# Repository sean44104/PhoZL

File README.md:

# PhobGCCv2-HW
Seperate repository for the hardware used in the PhobGCC v2.0

The PhobGCC v2.0 board is licensed under CERN Open Hardware Licence Version 2 - Strongly Reciprocal.
This means that any changes made to the board should be made public and CHANGES.txt be updated to reflect said changes.

# CHANGES.txt
PhoZL is a version of the PhobGCCv2 PCB that adds a footprint for a left z button to the board, connecting to GND and GPIO12

In order to make these changes possible, the edge cuts and the tracks inside of the PCB have been modified; these changes are self evident.

PCB Ordering Guide: https://github.com/PhobGCC/PhobGCC-doc/blob/main/For_Makers/Phob2_JLCPCB_Ordering_Guide.md

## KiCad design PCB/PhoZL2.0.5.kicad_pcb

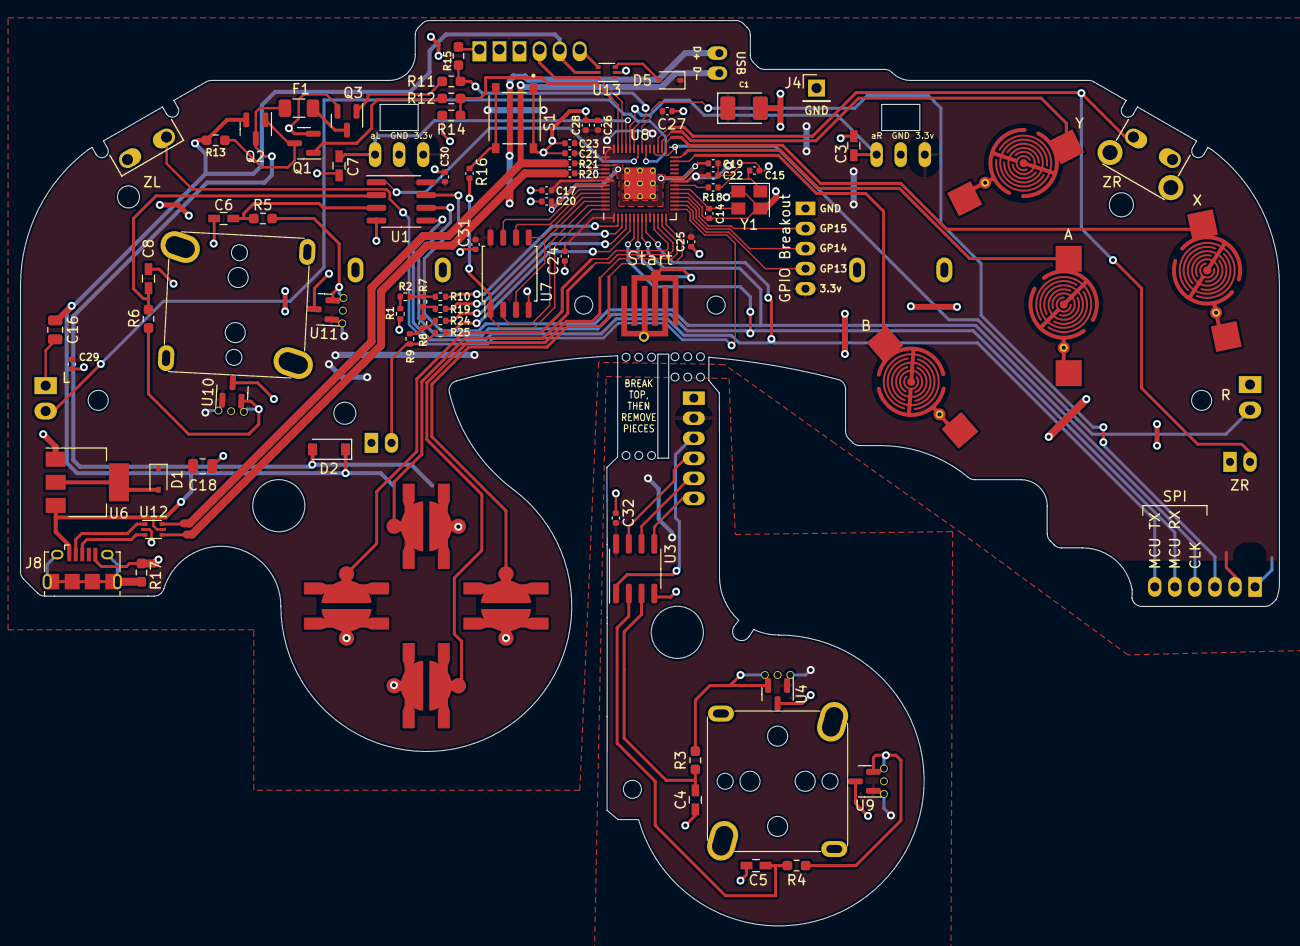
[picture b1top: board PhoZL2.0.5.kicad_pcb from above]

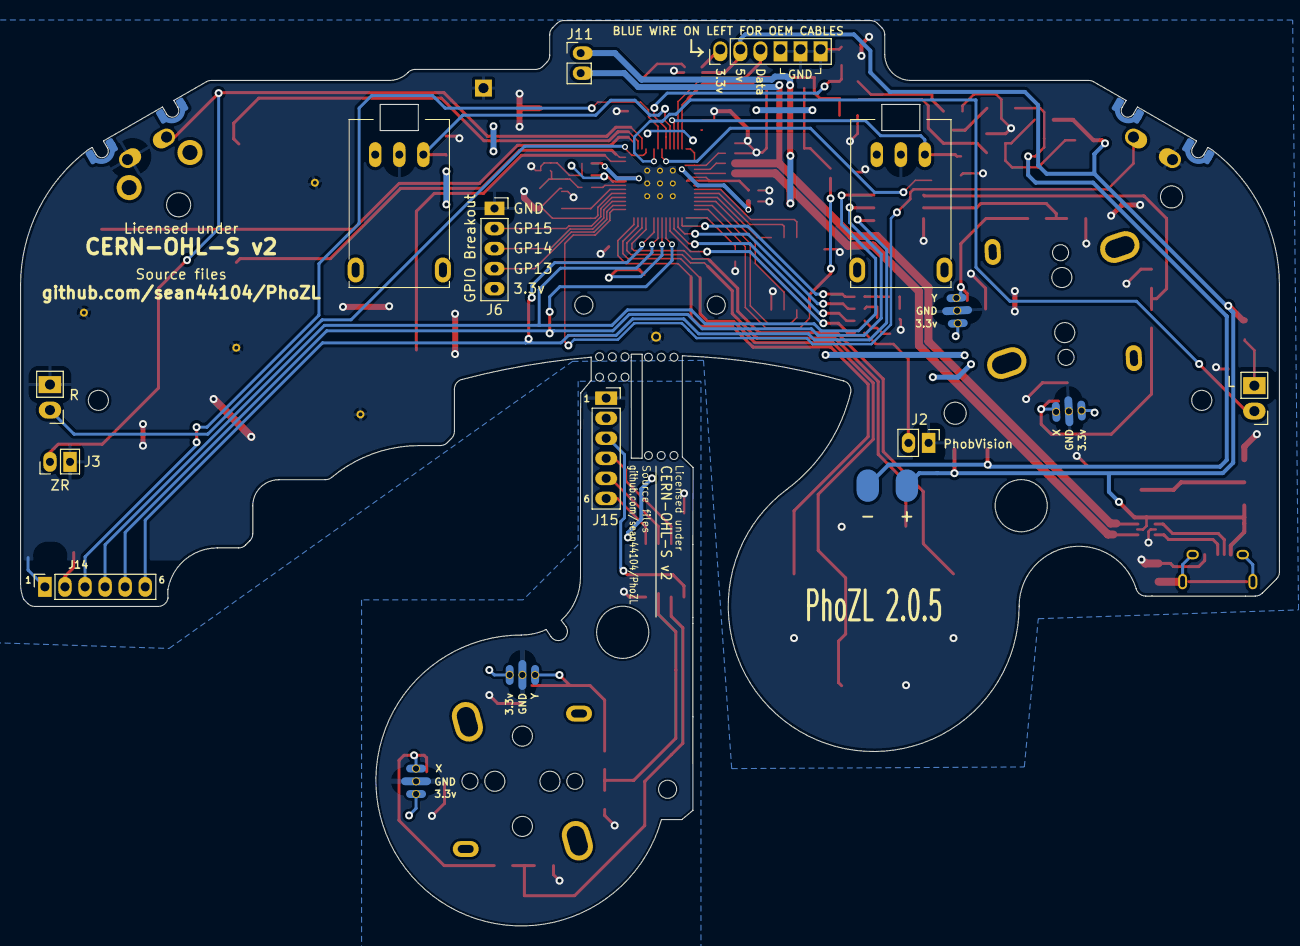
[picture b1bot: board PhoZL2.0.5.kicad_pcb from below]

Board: 2 copper layers, 125.5 x 90.3 mm, 111 parts (12 on the bottom side), 78 nets.

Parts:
C1: 47u; CP_EIA-3528-12_Kemet-T_Pad1.50x2.35mm_HandSolder
C3, C4, C5, C6, C7, C8: 0.047u; C_0603_HandSoldering
C14, C15: 27p; C_0402_1005Metric
C16, C18: 10u; C_0805_2012Metric
C17, C19, C20, C22, C24, C25, C26, C27, C28, C29, C30, C31, C32: 100n; C_0402_1005Metric
C21, C23: 1u; C_0402_1005Metric
D1, D5: CUS10S30,H3F; D_SOD-323
D2: M7C; D_SOD-123
F1: Fuse; Fuse_1206_3216Metric
H1: 5.2mm; MountingHole_5.2mm
H2: Slot
H3, H4: 2mm; MountingHole_2.0mm
H5, H6: 1.8mm; MountingHole_1.8mm
H7: 2.4mm; MountingHole_2.4mm
H8, H9: 2.2mm; MountingHole_2.2mm
H10: MountingHole; MountingHole_1.8mm
H11: MountingHole; MountingHole_5.2mm
H12, H13: MountingHole; MountingHole_2.0mm
H14: MouseBite; breakaway-mousebites-double-v2-small
H15: MouseBite; breakaway-mousebites-double-v2-large
J1: Conn_01x06_Female; GCC_Header_Straight_1x06_Pitch2.00mm
J2, J11: Conn_01x02; PinHeader_1x02_P2.00mm_Vertical
J3: Conn_01x02; PinHeader_1x02_P2.00mm_Horizontal
J4: Conn_01x01; PinHeader_1x01_P2.54mm_Vertical
J5: Rumble; rumble_pins
J6, J14, J15: Conn_01x06; PinSocket_1x06_P2.00mm_Vertical
J8: USB_B_Micro; USB_Micro-B_Amphenol_10118194_Horizontal
Q1, Q3: Q_NMOS_GSD; SOT-23
Q2: Q_PMOS_GDS; SOT-23
R1, R2, R7, R8, R9: 180; R_0402_1005Metric
R3, R4, R5, R6: 2k; R_0603_1608Metric_Pad0.98x0.95mm_HandSolder
R10, R19, R24, R25: 316; R_0402_1005Metric
R11, R12: 100R; R_0603_1608Metric_Pad0.98x0.95mm_HandSolder
R13, R14, R15: 10k; R_0603_1608Metric_Pad0.98x0.95mm_HandSolder
R16, R18: 1k; C_0402_1005Metric
R17: 100k; R_0603_1608Metric_Pad0.98x0.95mm_HandSolder
R20, R21: 27; C_0402_1005Metric
RV1, RV2: R_POT_MountingPin; GCC_Slider
S1: BOOTSEL; SW_TS-1187A-B-A-B
SW1: A; ABXY_Contact_Omron_Switch_Circley
SW2: B; ABXY_Contact_Omron_Switch_Circley
SW3: X; ABXY_Contact_Omron_Switch_Circley
SW4: Y; ABXY_Contact_Omron_Switch_Circley
SW5: Start; Start_Contact
SW6: L; Pin_Header_Straight_1x02_Pitch2.54mm
SW7: R; Pin_Header_Straight_1x02_Pitch2.54mm
SW8, SW8#2: Z; Z_Switch_Edge_Omron
SW9: Dleft; Dpad_Contact_TL3315NF_2
SW10: Dup; Dpad_Contact_TL3315NF_2
SW11: Dright; Dpad_Contact_TL3315NF_2
SW12: Ddown; Dpad_Contact_TL3315NF_2
U1, U3: MCP3202; SOIC-8_3.9x4.9mm_P1.27mm
U2: Stickbox_Assembly_Main; GCC_Stickbox_Hall_Only
U4, U9, U10, U11: DRV5055A3xDBZxQ1; SOT-23
U5: Stickbox_Assembly_CStick; GCC_Stickbox_Hall_Only
U6: AMS1117-3.3; SOT-223-3_TabPin2
U7: W25Q128JVS; SOIC-8_5.23x5.23mm_P1.27mm
U8: RP2040; RP2040-QFN-56
U12, U13: USBLC6-2P6; SOT-666
Y1: Crystal_GND24; Crystal_SMD_3225-4Pin_3.2x2.5mm

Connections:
+1V1: C19.1, C20.1, C21.1, U8.23 (DVDD), U8.45 (VREG_VOUT), U8.50 (DVDD)
+3V3: C1.1, C17.1, C18.1, C22.1, C23.1, C24.1, C25.1, C26.1, C27.1, C28.1, C29.1, C30.1, C31.1, D1.1 (K), D5.1 (K), J6.2, J14.2, RV1.1 (V+), RV2.1 (V+), U1.8 (VDD/VREF), U2.1 (H1XV), U2.4 (H1YV), U7.8 (VCC), U8.1 (IOVDD), U8.10 (IOVDD), U8.22 (IOVDD), U8.33 (IOVDD), U8.42 (IOVDD), U8.43 (ADC_AVDD), U8.44 (VREG_IN), U8.48 (USB_VDD), U8.49 (IOVDD), U10.1 (VCC), U11.1 (VCC)
+5V: C16.1, D2.1 (K), J1.2, J5.1, J8.1 (VBUS), Q2.2 (S), R13.2, U6.3 (VI), U12.5 (VBUS), U13.5 (VBUS)
/A: SW1.1, U8.28 (GPIO17)
/B: SW2.1, U8.27 (GPIO16)
/Brake: R12.1, R14.2, U8.41 (GPIO29_ADC3)
/CLK: J14.4, U1.7 (CLK), U8.8 (GPIO6)
/CLK2: J15.4, U3.7 (CLK)
/CS1: U1.1 (~CS/SHDN), U8.36 (GPIO24)
/CS2: J14.3, U8.35 (GPIO23)
/CS2_2: J15.3, U3.1 (~CS/SHDN)
/C_x_filt: C5.1, R4.1, U3.2 (CH0)
/C_y_filt: C4.1, R3.1, U3.3 (CH1)
/Ddown: SW12.1, U8.13 (GPIO10)
/Din: J14.6, U1.5 (DIN), U8.9 (GPIO7)
/Din2: J15.6, U3.5 (DIN)
/Dleft: SW9.1, U8.11 (GPIO8)
/Dout: J14.5, U1.6 (DOUT), U8.6 (GPIO4)
/Dout2: J15.5, U3.6 (DOUT)
/Dright: SW11.1, U8.14 (GPIO11)
/Dup: SW10.1, U8.12 (GPIO9)
/GCC_3.3V: J1.1, U13.4 (I/O2)
/GCC_DATA: J1.3, U8.40 (GPIO28_ADC2), U13.6 (I/O1)
/GND_C: C4.2, C5.2, C32.2, J15.1, U3.4 (VSS), U4.3 (GND), U5.2 (H1XG), U5.5 (H1YG), U9.3 (GND)
/GPIO12: SW8#2.2, U8.15 (GPIO12)
/GPIO13: J6.3, U8.16 (GPIO13)
/GPIO14: J6.4, U8.17 (GPIO14)
/GPIO15: J6.5, U8.18 (GPIO15)
/H1XS: R6.2, U2.3 (H1XS), U10.2 (OUT)
/H1YS: R5.2, U2.6 (H1YS), U11.2 (OUT)
/H2XS: R4.2, U5.3 (H1XS), U9.2 (OUT)
/H2YS: R3.2, U4.2 (OUT), U5.6 (H1YS)
/L: SW6.1, U8.34 (GPIO22)
/Ladder1: R10.2, U8.2 (GPIO0)
/Ladder2: R19.2, U8.3 (GPIO1)
/Ladder3: R24.2, U8.4 (GPIO2)
/Ladder4: R25.2, U8.5 (GPIO3)
/Lanalog: C7.1, RV1.3 (Signal), U8.39 (GPIO27_ADC1)
/QSPI_SCLK: U7.6 (CLK), U8.52 (QSPI_SCLK)
/QSPI_SD0: U7.5 (DI(IO0)), U8.53 (QSPI_SD0)
/QSPI_SD1: U7.2 (DO(IO1)), U8.55 (QSPI_SD1)
/QSPI_SD2: U7.3 (IO2), U8.54 (QSPI_SD2)
/QSPI_SD3: U7.7 (IO3), U8.51 (QSPI_SD3)
/QSPI_SS: R16.1, U7.1 (~CS), U8.56 (QSPI_SS)
/R: SW7.1, U8.32 (GPIO21)
/Ranalog: C3.1, RV2.3 (Signal), U8.38 (GPIO26_ADC0)
/Rumble: R11.1, R15.2, U8.37 (GPIO25)
/Start: SW5.1, U8.7 (GPIO5)
/Stick_x_filt: C8.1, R6.1, U1.2 (CH0)
/Stick_y_filt: C6.1, R5.1, U1.3 (CH1)
/USB_D+: J11.1, R20.1, U12.4 (I/O2)
/USB_D+_Raw: J8.3 (D+), U12.3 (I/O2)
/USB_D-: J11.2, R21.1, U12.6 (I/O1)
/USB_D-_Raw: J8.2 (D-), U12.1 (I/O1)
/V: J2.2, R9.1, R25.1
/X: SW3.1, U8.29 (GPIO18)
/XIN: C14.1, U8.20 (XIN), Y1.3
/XOUT: R18.1, U8.21 (XOUT)
/Y: SW4.1, U8.30 (GPIO19)
/Z: J3.2, SW8.1, U8.31 (GPIO20)
/~USB_BOOT: R16.2, S1.C, S1.D
GND: C1.2, C3.2, C6.2, C7.2, C8.2, C14.2, C15.2, C16.2, C17.2, C18.2, C19.2, C20.2, C21.2, C22.2, C23.2, C24.2, C25.2, C26.2, C27.2, C28.2, C29.2, C30.2, C31.2, J1.4, J1.5, J1.6, J2.1, J3.1, J4.1, J6.6, J8.5 (GND), J14.1, Q1.2 (S), Q3.2 (S), R1.2, R14.1, R15.1, R17.2, RV1.2 (GND), RV2.2 (GND), S1.A, S1.B, SW1.2, SW2.2, SW3.2, SW4.2, SW5.2, SW6.2, SW7.2, SW8.2, SW8#2.1, SW9.2, SW10.2, SW11.2, SW12.2, U1.4 (VSS), U2.2 (H1XG), U2.5 (H1YG), U6.1 (GND), U7.4 (GND), U8.19 (TESTEN), U8.57 (GND), U10.3 (GND), U11.3 (GND), U12.2 (GND), U13.2 (GND), Y1.2, Y1.4
unnamed: C15.1, R18.2, Y1.1
unnamed: D1.2 (A), U6.2 (VO)
unnamed: D2.2 (A), F1.1, J5.2, Q2.3 (D)
unnamed: D5.2 (A), U13.3 (I/O2)
unnamed: F1.2, Q3.3 (D)
unnamed: J8.6 (Shield), R17.1
unnamed: Q1.1 (G), R12.2
unnamed: Q1.3 (D), Q2.1 (G), R13.1
unnamed: Q3.1 (G), R11.2
unnamed: R1.1, R2.2
unnamed: R2.1, R7.2, R10.1
unnamed: R7.1, R8.2, R19.1
unnamed: R20.2, U8.47 (USB_DP)
unnamed: R21.2, U8.46 (USB_DM)
unnamed: R8.1, R9.2, R24.1
VCC: C32.1, J15.2, U3.8 (VDD/VREF), U4.1 (VCC), U5.1 (H1XV), U5.4 (H1YV), U9.1 (VCC)

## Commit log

2022-12-13 altered the files on my fork to reflect the changes described in changes.txt
2022-12-13 added images and updated the silkscreen
2022-12-13 put the images into a folder
2022-12-13 image display and gerbers
2022-12-16 12-16-22 Changes
    pcb has been redone on the newest version of the 2.0.2 pcb
    (my dpad was added to the main pcb!)
    gpio15 on zl changed to gpio12
    removed the zl input from the GPIO breakout, instead going directly into the rp2040
2022-12-20 12-20-22 Changes
    slight updates to the silkscreen
    USB Data + / - as well as the GND at the top of the PCB has been relocated
    (Credit to Plants for the idea!)
2022-12-23 12-23-22 Changes
    updated dpad to match current phob 2
2023-05-31 2.0.5 Update
2023-10-23 Added PhoZL Software for v0.29
2023-11-06 more libs
2024-02-04 added a link to the purchase guide

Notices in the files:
PCB/PhoZL2.0.5.kicad_pcb:
CERN-OHL-S v2
